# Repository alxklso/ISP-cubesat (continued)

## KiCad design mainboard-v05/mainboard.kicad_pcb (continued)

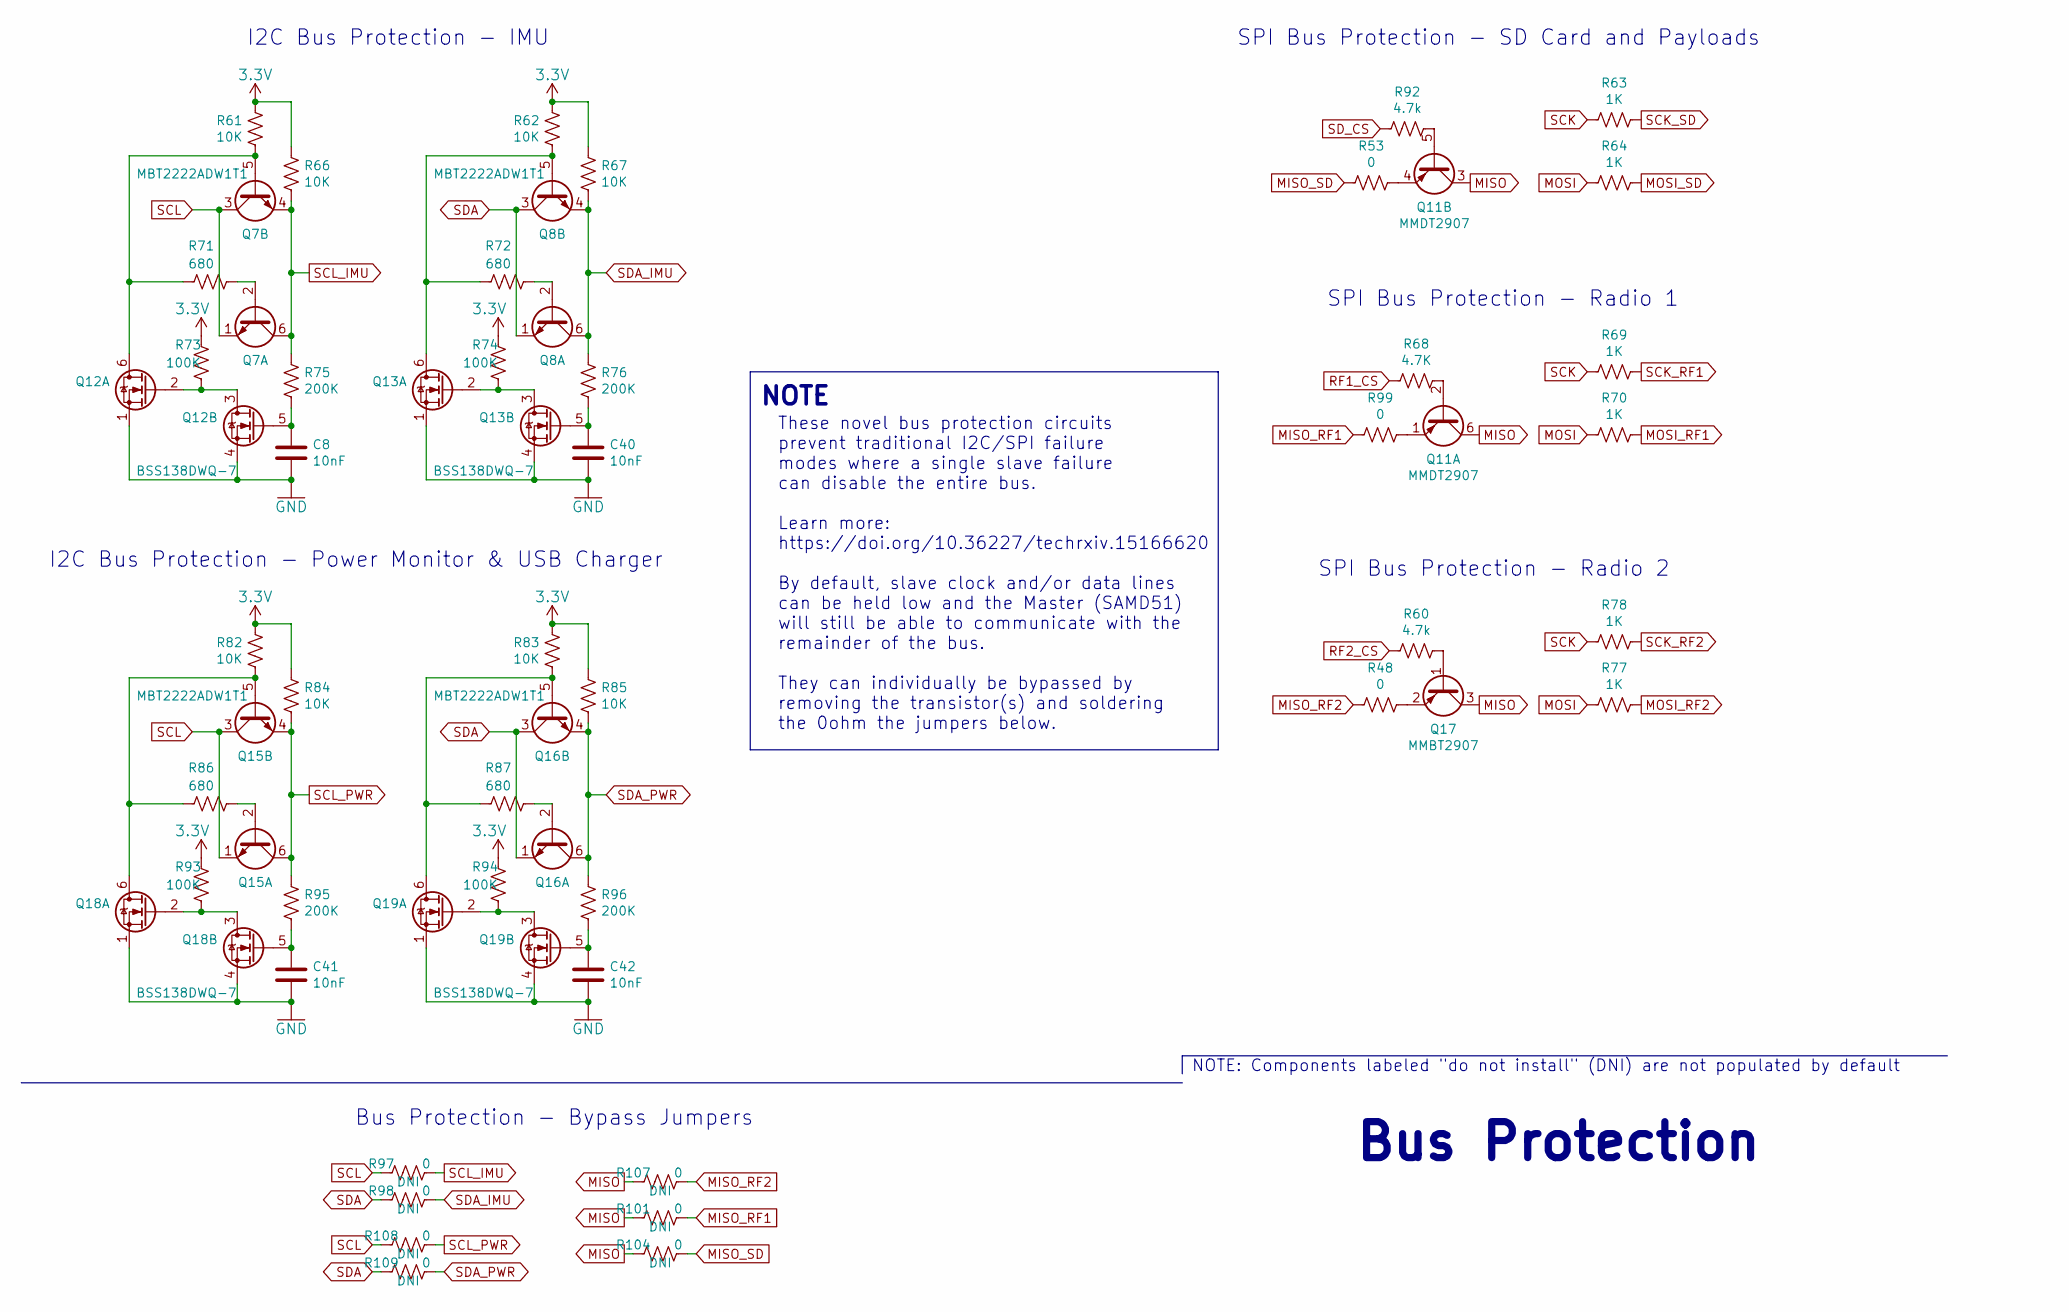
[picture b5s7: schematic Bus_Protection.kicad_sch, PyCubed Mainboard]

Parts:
C8, C40, C41, C42: 10nF; C_0603_1608Metric
Q7, Q8, Q15, Q16: MBT2222ADW1T1; SOT-363_SC-70-6; Manufacturer_Part_Number MBT2222ADW1T1G
Q11: MMDT2907; SOT-363_SC-70-6; Manufacturer_Part_Number MMDT2907AQ-7-F
Q12, Q13, Q18, Q19: BSS138DWQ-7; Manufacturer_Part_Number BSS138DWQ-7
Q17: MMBT2907; SOT-23; Manufacturer_Part_Number MMBT2907ALT1G
R48, R53, R97, R98, R99, R101, R104, R107, R108, R109: 0; R_0603_1608Metric
R60, R92: 4.7k; R_0603_1608Metric
R61, R62, R66, R67, R82, R83, R84, R85: 10K; R_0603_1608Metric
R63, R64, R69, R70, R77, R78: 1K; R_0603_1608Metric
R68: 4.7K; R_0603_1608Metric
R71, R72, R86, R87: 680; R_0603_1608Metric
R73, R74, R93, R94: 100K; R_0603_1608Metric
R75, R76, R95, R96: 200K; R_0603_1608Metric

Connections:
3.3V: R61.1, R62.1, R66.1, R67.1, R73.1, R74.1, R82.1, R83.1, R84.1, R85.1, R93.1, R94.1; also elsewhere on the board
GND: C8.2, C40.2, C41.2, C42.2, Q12.1 (S2), Q12.4 (S1), Q13.1 (S2), Q13.4 (S1), Q18.1 (S2), Q18.4 (S1), Q19.1 (S2), Q19.4 (S1); also elsewhere on the board
MISO: Q11.3 (C2), Q11.6 (C1), Q17.3 (C), R101.2, R104.2, R107.2; also elsewhere on the board
MISO_RF1: R99.2, R101.1; also elsewhere on the board
MISO_RF2: R48.2, R107.1; also elsewhere on the board
MISO_SD: R53.2, R104.1; also elsewhere on the board
MOSI: R64.2, R70.1, R77.2; also elsewhere on the board
MOSI_RF1: R70.2; also elsewhere on the board
MOSI_RF2: R77.1; also elsewhere on the board
MOSI_SD: R64.1; also elsewhere on the board
unnamed: C8.1, Q12.5 (G1), R75.2
unnamed: C40.1, Q13.5 (G1), R76.2
unnamed: C41.1, Q18.5 (G1), R95.2
unnamed: C42.1, Q19.5 (G1), R96.2
unnamed: Q7.2 (B1), R71.1
unnamed: Q8.2 (B1), R72.1
unnamed: Q11.1 (E1), R99.1
unnamed: Q11.2 (B1), R68.1
unnamed: Q11.4 (E2), R53.1
unnamed: Q11.5 (B2), R92.1
unnamed: Q12.2 (G2), Q12.3 (D2), R73.2
unnamed: Q7.5 (B2), Q12.6 (D1), R61.2, R71.2
unnamed: Q13.2 (G2), Q13.3 (D2), R74.2
unnamed: Q8.5 (B2), Q13.6 (D1), R62.2, R72.2
unnamed: Q15.2 (B1), R86.1
unnamed: Q15.5 (B2), Q18.6 (D1), R82.2, R86.2
unnamed: Q16.2 (B1), R87.1
unnamed: Q16.5 (B2), Q19.6 (D1), R83.2, R87.2
unnamed: Q17.1 (B), R60.1
unnamed: Q17.2 (E), R48.1
unnamed: Q18.2 (G2), Q18.3 (D2), R93.2
unnamed: Q19.2 (G2), Q19.3 (D2), R94.2
RF1_CS: R68.2; also elsewhere on the board
RF2_CS: R60.2; also elsewhere on the board
SCK: R63.2, R69.2, R78.2; also elsewhere on the board
SCK_RF1: R69.1; also elsewhere on the board
SCK_RF2: R78.1; also elsewhere on the board
SCK_SD: R63.1; also elsewhere on the board
SCL: Q7.1 (E1), Q7.3 (C2), Q15.1 (E1), Q15.3 (C2), R97.2, R108.2; also elsewhere on the board
SCL_IMU: Q7.4 (E2), Q7.6 (C1), R66.2, R75.1, R97.1; also elsewhere on the board
SCL_PWR: Q15.4 (E2), Q15.6 (C1), R84.2, R95.1, R108.1; also elsewhere on the board
SDA: Q8.1 (E1), Q8.3 (C2), Q16.1 (E1), Q16.3 (C2), R98.2, R109.2; also elsewhere on the board
SDA_IMU: Q8.4 (E2), Q8.6 (C1), R67.2, R76.1, R98.1; also elsewhere on the board
SDA_PWR: Q16.4 (E2), Q16.6 (C1), R85.2, R96.1, R109.1; also elsewhere on the board
SD_CS: R92.2; also elsewhere on the board

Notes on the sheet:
NOTE
Bus Protection - Bypass Jumpers
I2C Bus Protection - Power Monitor & USB Charger
SPI Bus Protection - Radio 1
These novel bus protection circuits prevent traditional I2C/SPI failure modes where a single slave failure can disable the entire bus. Learn more: https://doi.org/10.36227/techrxiv.15166620 By default, slave clock and/or data lines can be held low and the Master (SAMD51) will still be able to commu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
NOTE: Components labeled "do not install" (DNI) are not populated by default
I2C Bus Protection - IMU
SPI Bus Protection - Radio 2
SPI Bus Protection - SD Card and Payloads
Bus Protection

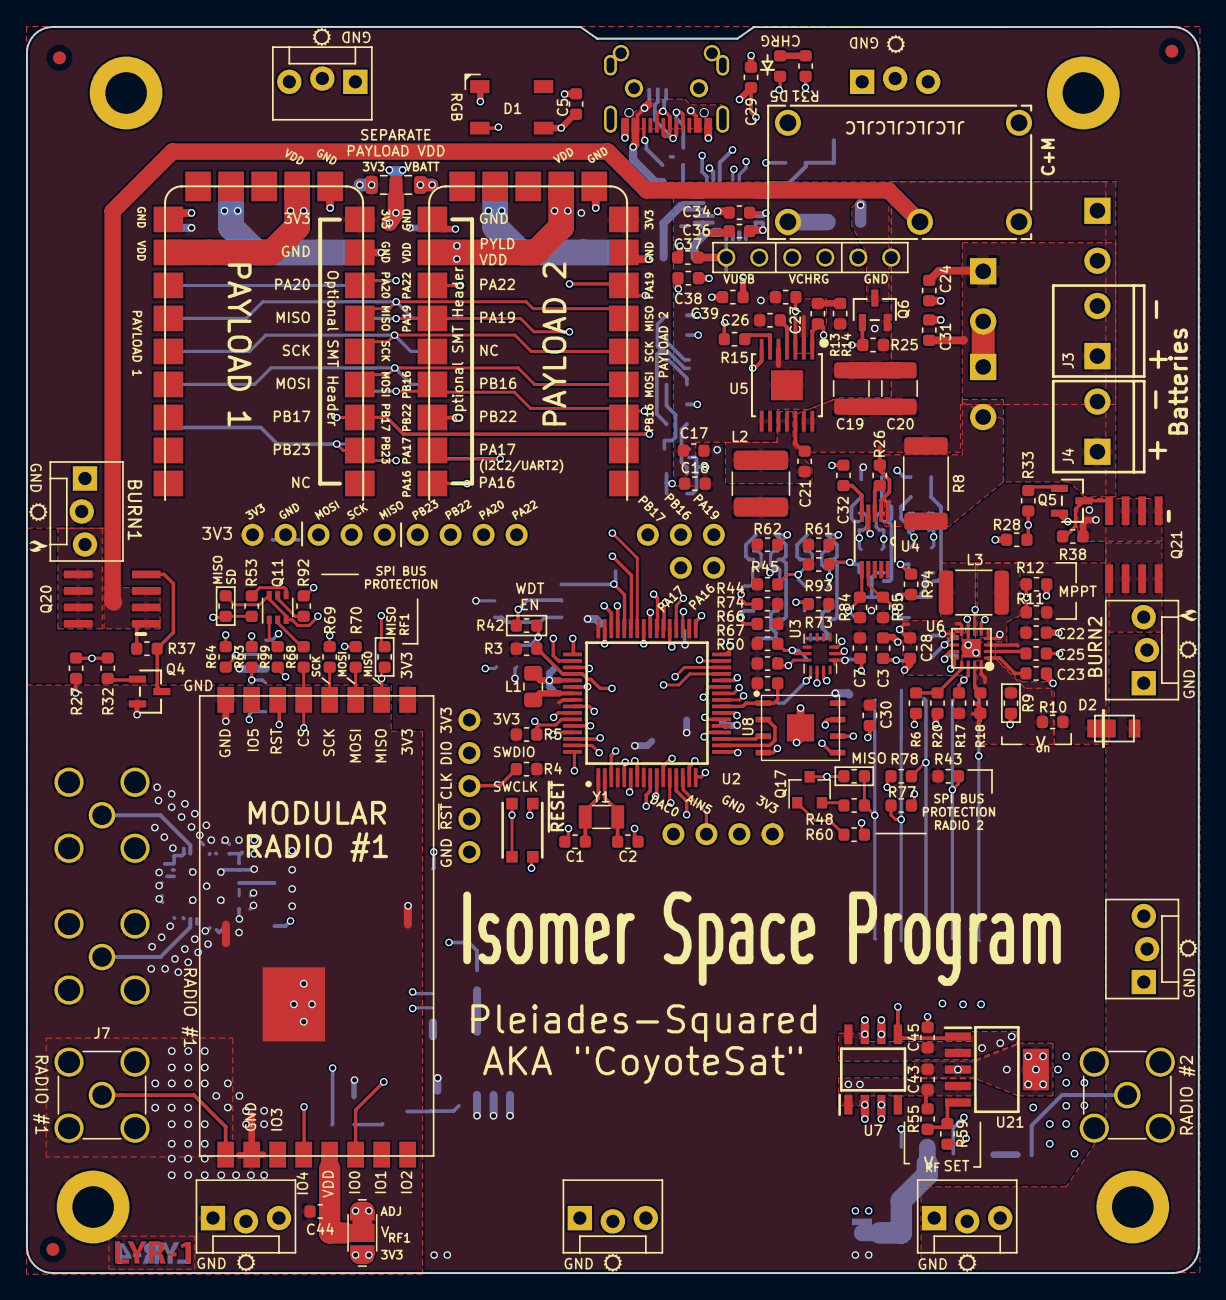
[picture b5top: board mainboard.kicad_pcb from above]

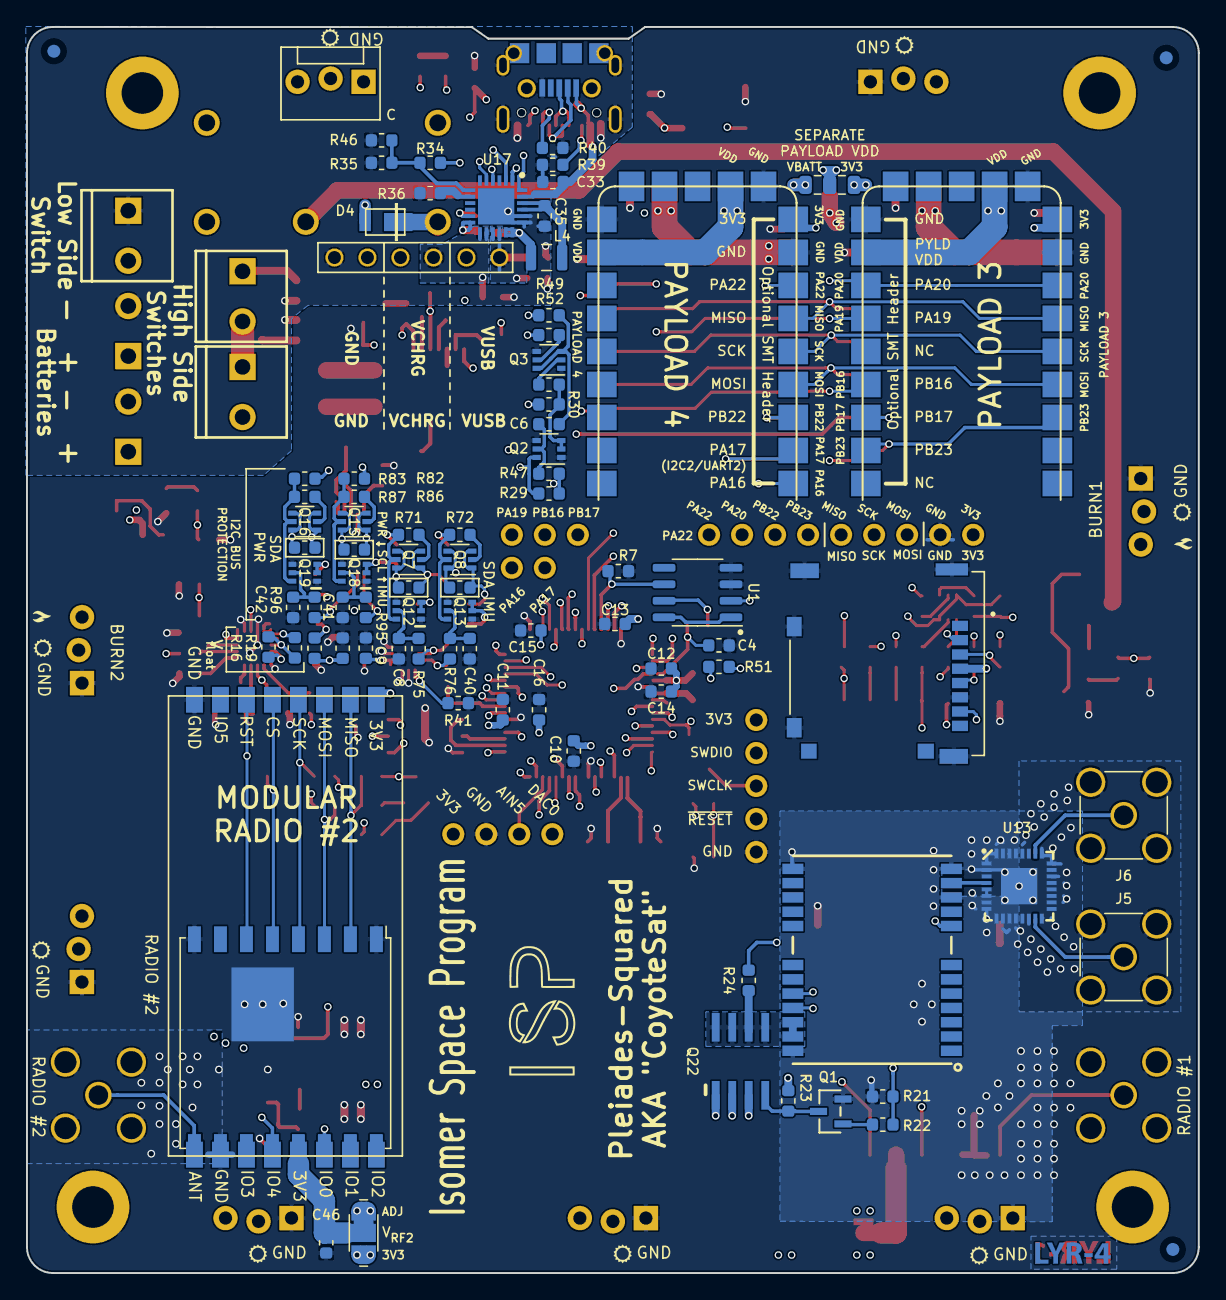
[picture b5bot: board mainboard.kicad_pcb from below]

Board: 4 copper layers, 90.2 x 95.9 mm, 230 parts (91 on the bottom side), 160 nets.

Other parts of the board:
REF1B, REF1T, REF2B, REF2T, REF3B, REF3T: Fiducial_1mm_Mask2mm

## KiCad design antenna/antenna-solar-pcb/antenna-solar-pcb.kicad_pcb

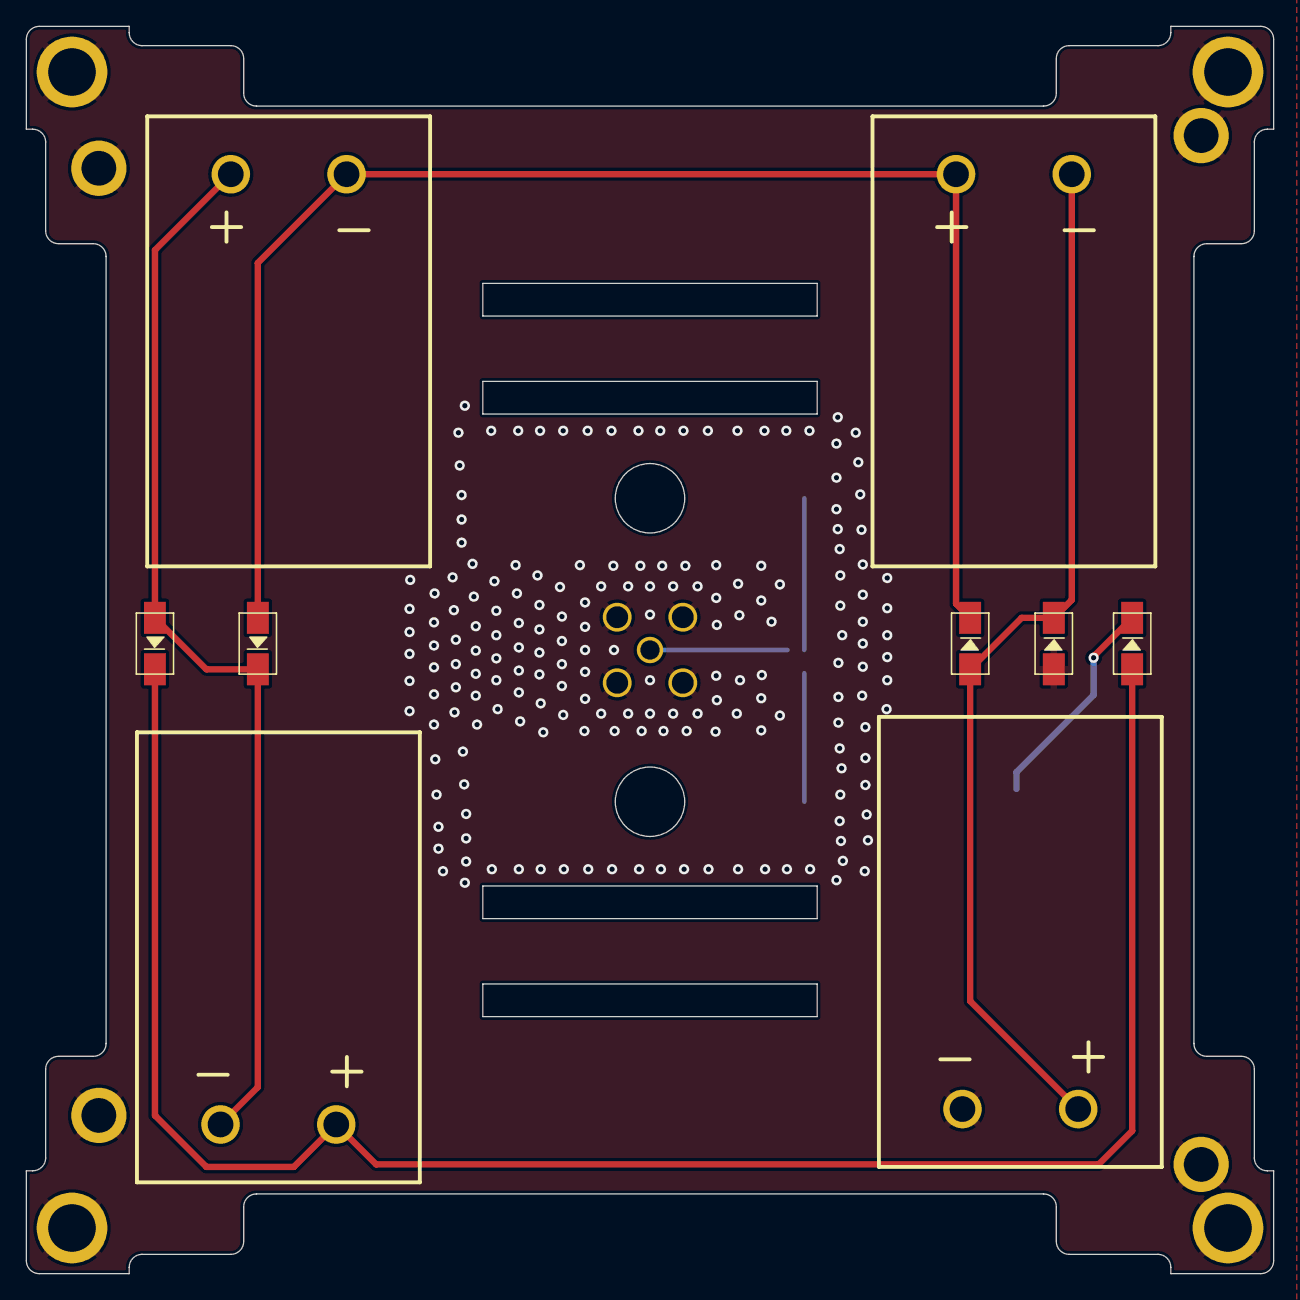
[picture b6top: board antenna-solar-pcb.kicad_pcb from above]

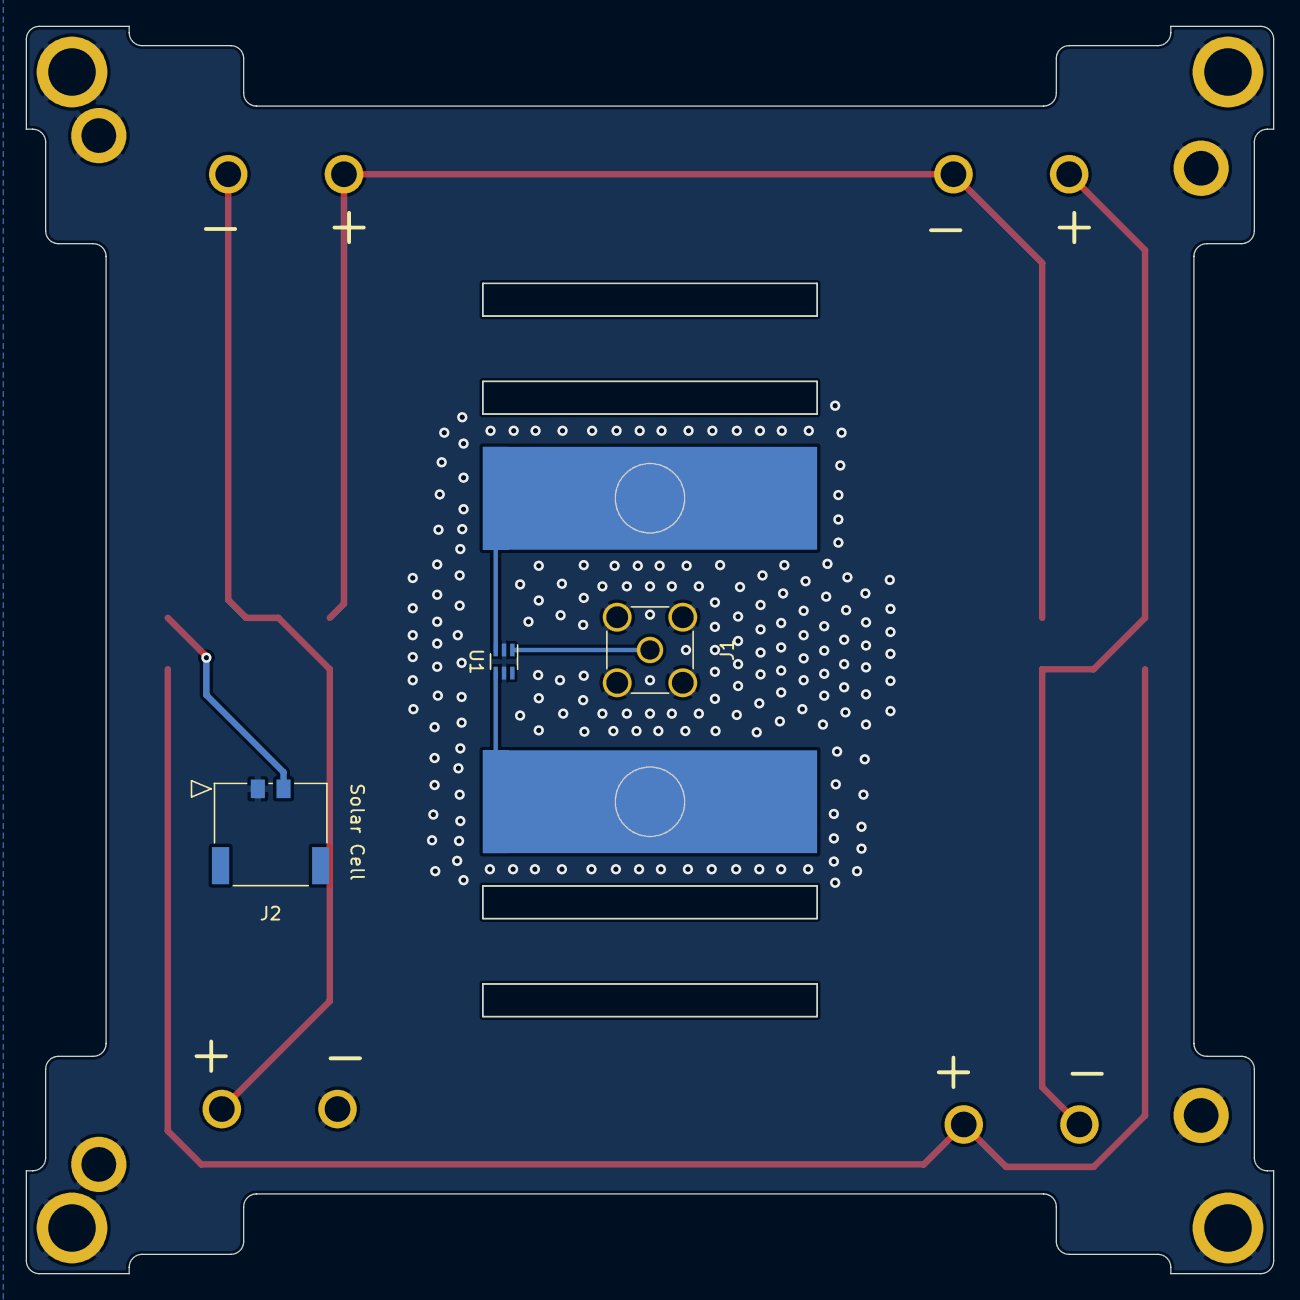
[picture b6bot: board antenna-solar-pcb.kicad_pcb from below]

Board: 2 copper layers, 97.0 x 97.0 mm, 21 parts (4 on the bottom side), 9 nets.

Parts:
AE1: Dipole_Antenna; Antenna_Pads
D1, D2, D3, D4, D5: CDBA240LL-HF; DO-214AC
H1, H2, H3, H4: MountingHole_Pad; MountingHole_3.7mm_Pad_Modified
H5, H6, H7, H8: MountingHole_Pad; MountingHole_2.7mm_M2.5_DIN965_Pad
J1: SMA Connector Male; SMA_Connector
J2: Solar Cell; pico_lock_2mm_2circuit
SC1, SC2, SC3, SC4: SM101K07TF
U1: HHM1589D1; Balun_Johanson_5400BL15B050E

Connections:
GND: D4.2 (A), H1.1, H2.1, H3.1, H4.1, H5.1, H6.1, H7.1, H8.1, J1.2 (Ext), J2.1, SC4.2 (-), U1.2 (GND), U1.5 (GND)
unnamed: AE1.1, U1.3 (Balanced_Port)
unnamed: AE1.2, U1.4 (Balanced_Port)
unnamed: D1.1 (K), D5.2 (A), SC1.1 (+)
unnamed: D1.2 (A), D2.1 (K), SC1.2 (-), SC2.1 (+)
unnamed: D2.2 (A), D3.1 (K), SC2.2 (-), SC3.1 (+)
unnamed: D3.2 (A), D4.1 (K), SC3.2 (-), SC4.1 (+)
unnamed: J1.1 (In), U1.1 (Balanced_Port)
VSOLAR: D5.1 (K), J2.2

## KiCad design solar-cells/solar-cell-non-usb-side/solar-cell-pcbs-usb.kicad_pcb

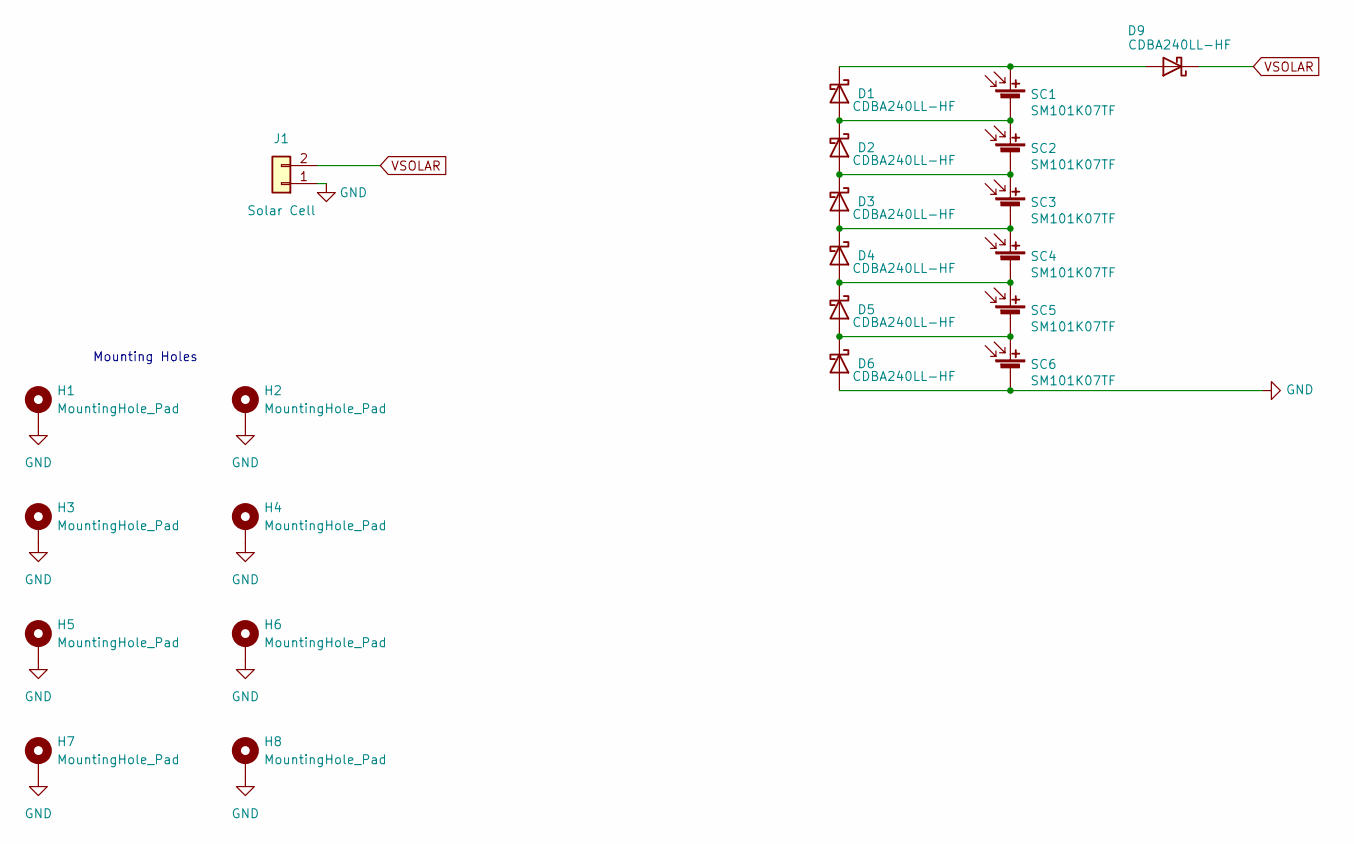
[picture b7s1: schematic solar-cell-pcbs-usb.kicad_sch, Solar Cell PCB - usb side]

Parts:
D1, D2, D3, D4, D5, D6, D9: CDBA240LL-HF; DO-214AC
H1, H2, H3, H4, H5, H6, H7, H8: MountingHole_Pad; MountingHole_3.2mm_M3_DIN965_Pad
J1: Solar Cell; 2053380002
SC1, SC2, SC3, SC4, SC5, SC6: SM101K07TF

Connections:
GND: D6.2 (A), H1.1, H2.1, H3.1, H4.1, H5.1, H6.1, H7.1, H8.1, J1.1, SC6.2 (-)
unnamed: D1.1 (K), D9.2 (A), SC1.1 (+)
unnamed: D1.2 (A), D2.1 (K), SC1.2 (-), SC2.1 (+)
unnamed: D2.2 (A), D3.1 (K), SC2.2 (-), SC3.1 (+)
unnamed: D3.2 (A), D4.1 (K), SC3.2 (-), SC4.1 (+)
unnamed: D4.2 (A), D5.1 (K), SC4.2 (-), SC5.1 (+)
unnamed: D5.2 (A), D6.1 (K), SC5.2 (-), SC6.1 (+)
VSOLAR: D9.1 (K), J1.2

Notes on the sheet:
Mounting Holes

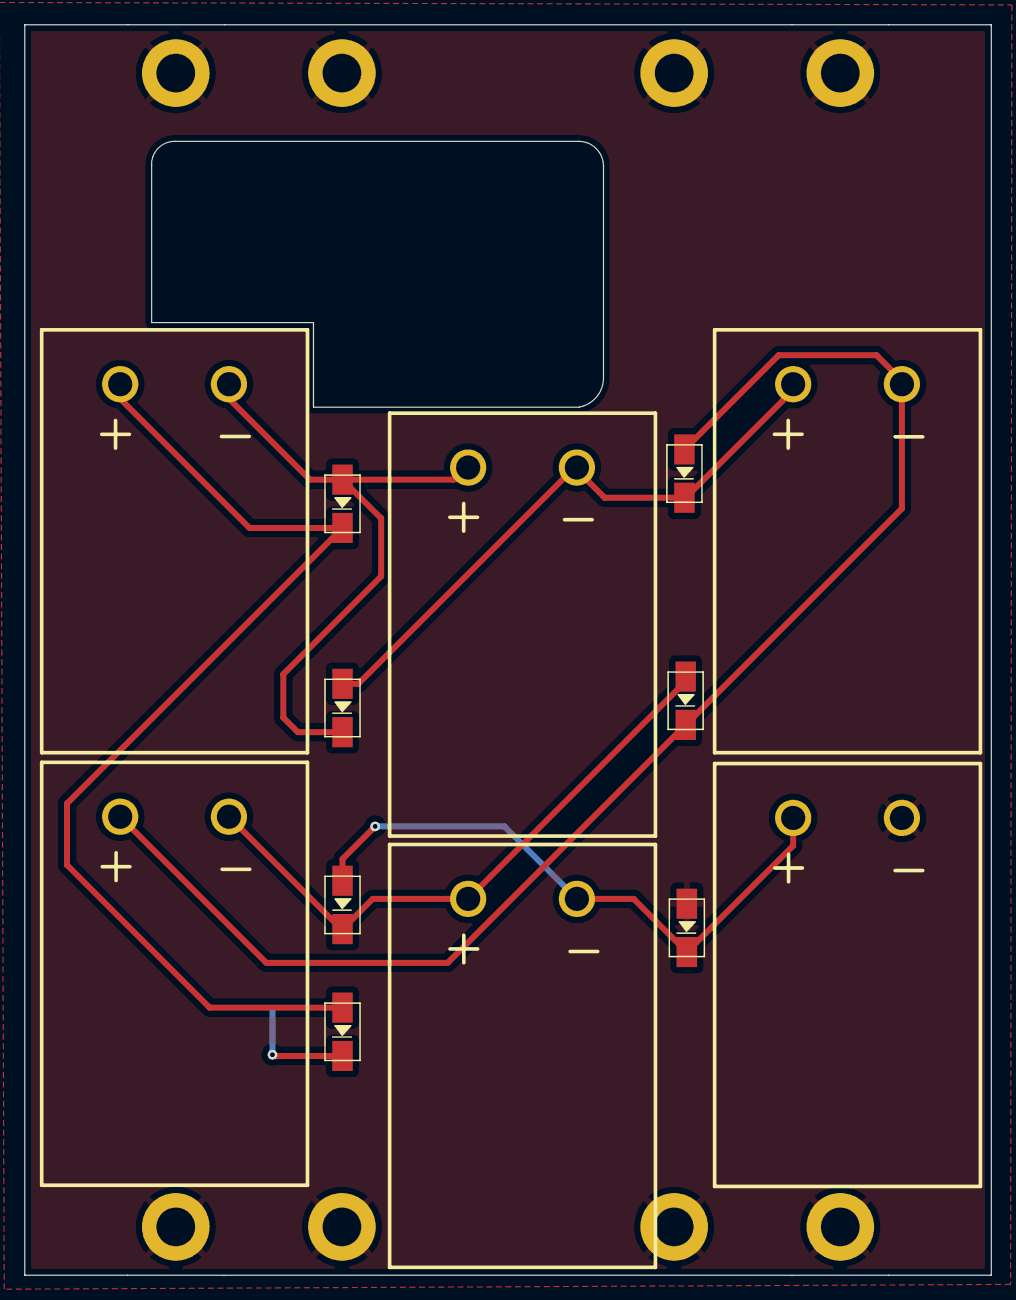
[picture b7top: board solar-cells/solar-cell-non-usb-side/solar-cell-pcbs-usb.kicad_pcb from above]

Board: 2 copper layers, 80.0 x 103.5 mm, 22 parts (1 on the bottom side), 8 nets.

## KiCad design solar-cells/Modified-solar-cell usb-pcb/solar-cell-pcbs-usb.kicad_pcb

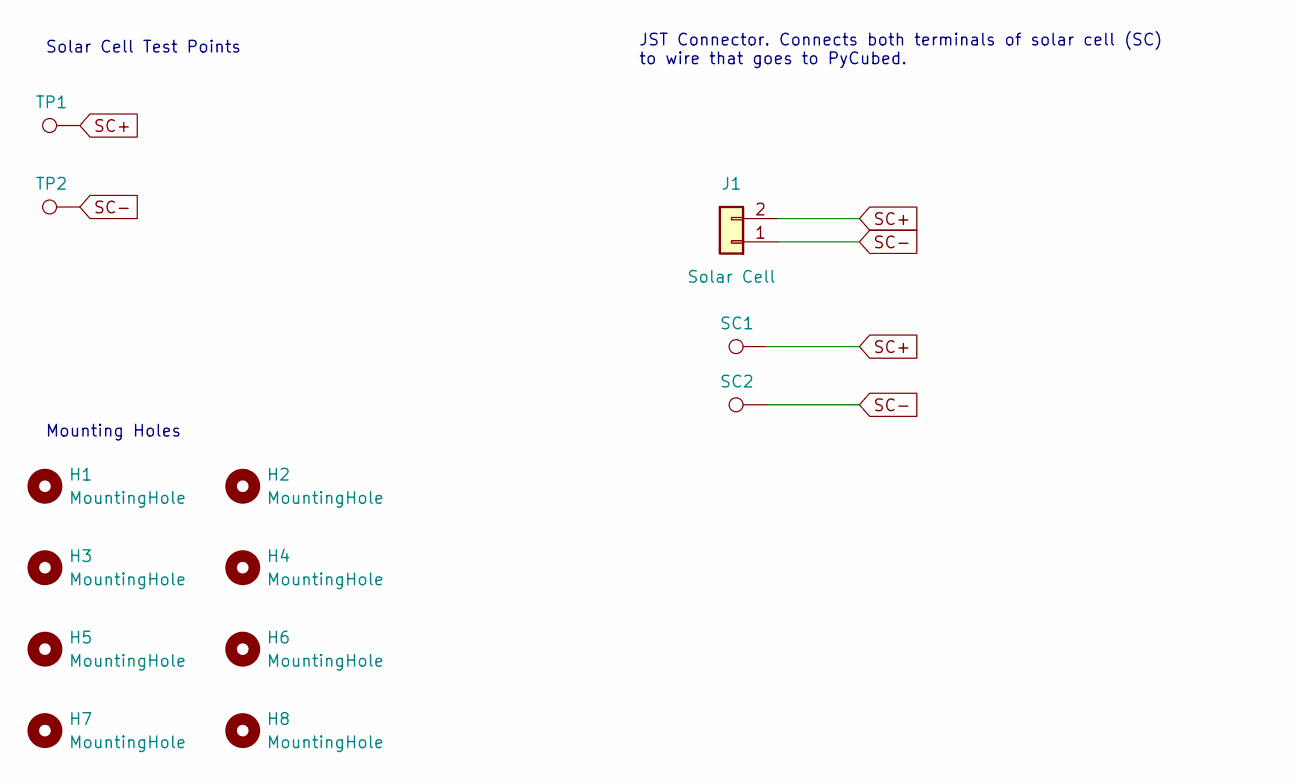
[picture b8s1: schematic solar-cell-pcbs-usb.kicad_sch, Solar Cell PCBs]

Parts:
H1, H2, H3, H4, H5, H6, H7, H8: MountingHole; MountingHole_3.2mm_M3_DIN965_Pad
J1: Solar Cell; 2053380002
SC1: SC+; TestPoint_THTPad_D3.0mm_Drill1.5mm
SC2: SC-; TestPoint_THTPad_D3.0mm_Drill1.5mm
TP1: SC+; TestPoint_Loop_D1.80mm_Drill1.0mm_Beaded
TP2: SC-; TestPoint_Loop_D1.80mm_Drill1.0mm_Beaded

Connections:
SC+: J1.2, SC1.1, TP1.1
SC-: J1.1, SC2.1, TP2.1

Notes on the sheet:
Solar Cell Test Points
Mounting Holes
JST Connector. Connects both terminals of solar cell (SC) to wire that goes to PyCubed.

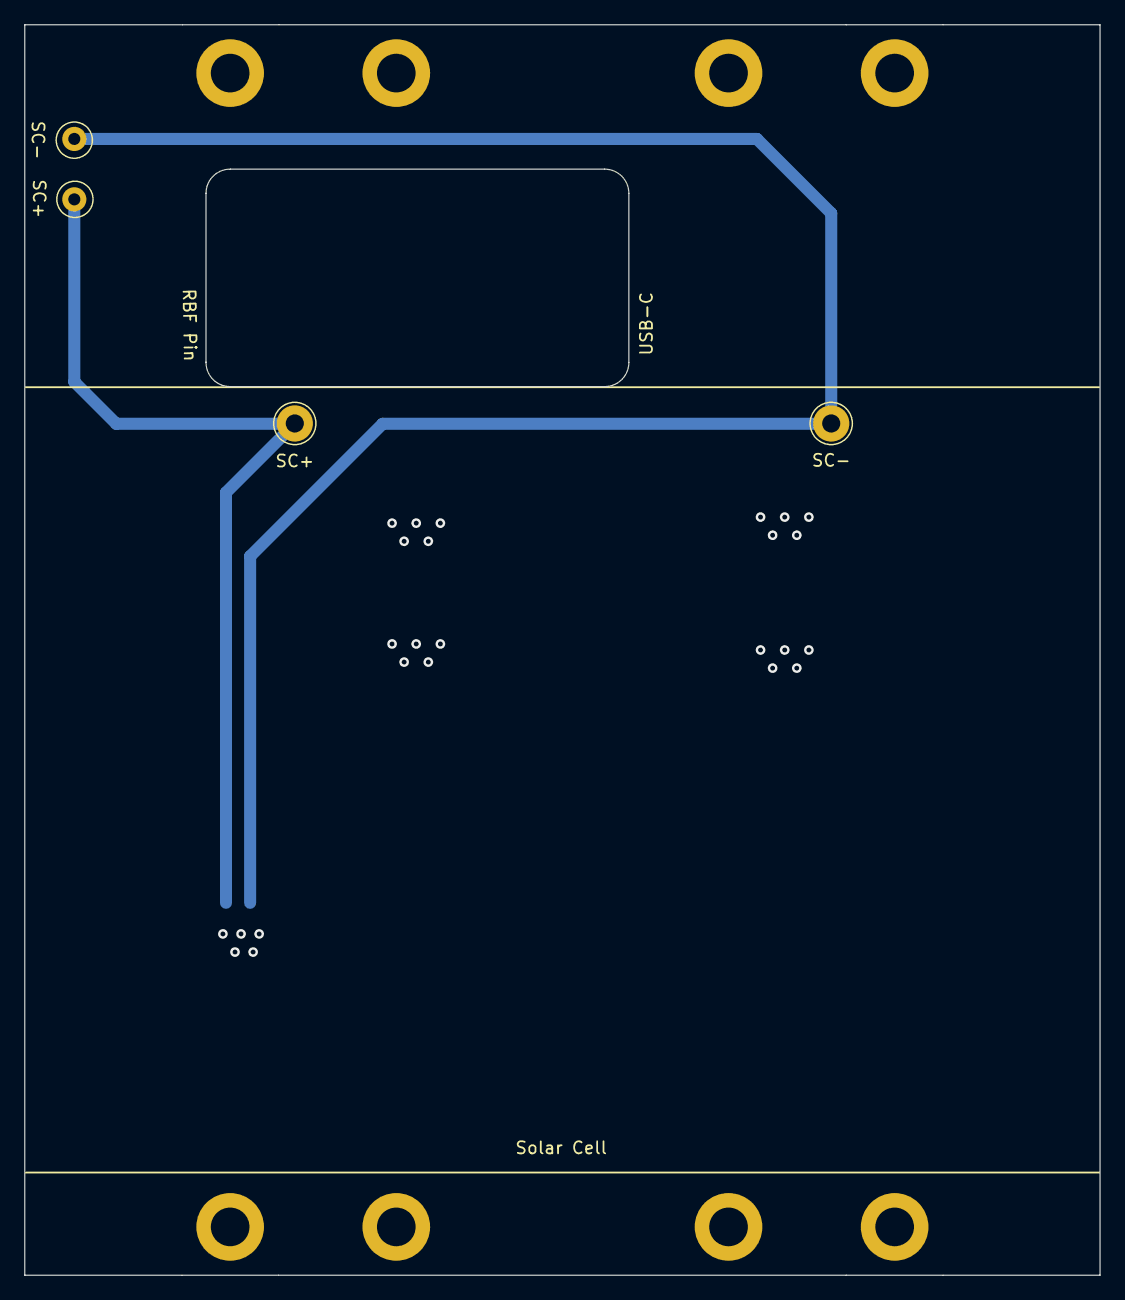
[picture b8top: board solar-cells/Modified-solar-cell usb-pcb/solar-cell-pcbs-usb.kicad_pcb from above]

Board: 2 copper layers, 89.0 x 103.5 mm, 13 parts (1 on the bottom side), 2 nets.

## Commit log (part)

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2022-07-16 Add files via upload
    gerber files for modified battery board
2022-07-21 Create blink.py
    Added prototyping and thing plus board folders, as well as blink test python file
2022-07-21 Add files via upload
    added light sensor test python file
2022-07-21 Create blink.py
    added new prototyping file and blink test python file
2022-07-21 Add files via upload
    added blink and light_sensor test python files for use with Thing Plus board (prototyping)
2022-08-15 Update light_sensor.py
    added more comments
2022-08-15 Add files via upload
    This is a file that does a simple channel scan for the TCA9548A multiplexer using a SAMD51 Thing Plus
2022-08-15 Rename light_sensor.py to ambient_light_sensor.py
    renamed
2022-08-15 Add files via upload
    Program for single VEML7700 lux sensor added
2022-08-19 Add files via upload
    Added file-writing functionality for sensor data
2022-08-19 Update four_lux_sensors.py
    fixed file format
2022-08-30 reorganized prototype folder
2022-08-30 added basic beepsat
2022-08-30 added mainboard files
2022-08-30 Update README.md
    Added annotations in README
2022-08-30 Update README.md
    Edited README
2022-09-07 added more prototyping folders
2022-09-07 fix again
2022-09-07 fixed file structure
2022-09-07 added more notes to README
2022-09-07 more notes to README
2022-09-24 added radio test software
2022-10-08 deleted IMU code
2022-10-12 added power consumption test py script
2022-10-15 added asyncioTest file
2022-10-15 lil fixes to asyncioTest
2022-10-18 adjusted code for Python 3.x syntax
2022-10-19 code changes to CW py script
2022-10-29 added test code for SD
2022-11-06 removed options 2,3, and moved up option 4 for script menu
2022-11-07 refactoring + deleting help info printing
2022-11-07 created datasheets folder and added solar cells data sheet
2022-11-12 re-uploaded beepsat-basic
2022-11-12 fixed formatting + module import error in main
2022-11-12 removed IMU code since no IMU is installed
2022-11-12 Added cosmic watch task file, and further formatting/annotating
2022-11-12 annotating main
2022-11-12 added gitignore
2022-11-12 Create LICENSE.md
    Added MIT License
2022-11-14 changed file layout
2022-11-16 added py script for logging CW data in terminal via USB
2022-11-16 added file-writing to CW datalogging script
2022-11-21 made separate folder for all CW stuff
2022-11-23 Updated CW script w file-writing and sample data file
2022-11-23 updated comments to serial port script
2022-11-23 moved comments to inside main
2022-12-09 added most recent sdWrite py script
2022-12-09 removed sdWrite file from beepsat-basic FSW, use the one in prototyping-CW until finalized
2022-12-09 updated CW script w/ comments and refactoring
2022-12-09 fix attempt
2022-12-10 Removed unnecessary sections of OLED arduino code
2022-12-12 made separate file for Arduino code to be used in space
2022-12-12 fixed CW task
2022-12-12 CW task now records data for 1 minute interval, still need to escape task tho
2022-12-12 modified main to be more helpful during debugging
2022-12-13 added radio test script and modified sdWrite to proto-pycubed folder
2022-12-13 Delete software/proto-CW/.idea directory
    deleted idea files
2022-12-18 Modified Arduino code to only record sipm voltage, also renamed OLED --> space
2022-12-18 Reorganized Arduino folder and updated README
2022-12-18 removed GPS and radio2 code
2022-12-19 new folder and kicad project for solar cell pcbs
2022-12-20 modified batt board to have wiring cutouts
2022-12-20 modifications to solar cell pcb
2022-12-21 modifications to solar cell pcbs with burn wires and usb cut out
2022-12-21 centering
2022-12-21 modifications to solar cell folder
2022-12-23 Create HI
2022-12-24 added cutouts and moved SMA connection point on mainboard
2022-12-25 fixed SMA connector issue and board cutouts
2022-12-25 sanity check commit
2022-12-25 added non-usb solar cell pcb side
2022-12-25 more annotations and connected test points
2022-12-25 removed thermal vias and fixed silkscreen
2022-12-25 change burn wire solar cell pcb to vertical
2022-12-25 removed OG usb solar cell pcb folder, not needed anymore
2022-12-25 modify non usb pcb
2022-12-25 name changes
2022-12-26 added more annotations
2022-12-26 update gitignore
2022-12-26 changes to non usb side
2022-12-26 changes to routes in burn wire pcb
2022-12-26 fixed mismatched traces
2022-12-26 measurement checking for non-usb and vertical burn pcbs
2022-12-26 remove silkscreen on footprint
2022-12-26 gerbers for non-usb and vertical burn created
2022-12-30 added beepsat advanced code
2022-12-30 deleted gps, radio2, and imu code
2022-12-30 fixed and formatted main
2022-12-30 added task for Cosmic Watch
2022-12-30 reformatting
2022-12-30 more formatting
2022-12-31 added antenna pcb folder
2022-12-31 create antenna pcb kicad prohect
2022-12-31 modified antenna pcb
2022-12-31 add antenna pcb with two slits on each side
2022-12-31 modify antenna pcbs and drc checked
2022-12-31 removed md file
2022-12-31 annotations
2022-12-31 fix dimensions
2022-12-31 add dimensions
2022-12-31 change sma connector hole size
2022-12-31 add kicad lib
2023-01-01 updated schematic for new solar cells
2023-01-01 hole positioning
2023-01-01 solar cell pcb laid out
2023-01-01 added usbc hole
2023-01-01 no edgecuts errors
2023-01-01 traces added
2023-01-01 new solar cell for burn wire side
2023-01-01 added silkscreens
2023-01-01 fixed mounting holes
2023-01-01 hole fixing
2023-01-01 hole removal
2023-01-01 directory reorg
2023-01-01 add new new solar cell pcb for burn wire side
2023-01-01 removed extra measurements from new new
2023-01-01 fixing up usb side
2023-01-01 check for new new
2023-01-01 created bottom adapter plate w/ solar cells
2023-01-01 bottom adapter plate sanity commit
2023-01-01 placed components, added traces to antenna-solar
2023-01-01 added screw holes for antennas in antenna-solar
2023-01-02 adjusted for limit switches allowance
2023-01-02 moved GND hole to not interfere w/ chassis beam
2023-01-02 aligned burn wire holes
2023-01-02 added test software file for before + after vibration testing
2023-01-02 added pycubed.py and libraries to test software
2023-01-03 fixed annotations
2023-01-03 fixed disconnected track
2023-01-03 changed burn wire to 3s2p config
2023-01-03 fixed tracks to reduce EMI
2023-01-03 fixed bottom adapter to be 3s2p
2023-01-03 fixed tracks, added vias
2023-01-03 fixed routing, added vias
2023-01-03 final commit for bottom adapter w/ solar
2023-01-05 Moved item into loop
2023-01-06 rotated JST, fixed batt holder holes
2023-01-06 fixed something weird
2023-01-06 Revert "Moved item into loop"
    This reverts commit 62312068ed386dce9a1a4cf67fe31766c9685957.
2023-01-06 Revert "Added initial i2c code"
    This reverts commit f7e053b2185c1d86999f7e089d7532763f734a9c.
2023-01-06 added ISP graphic to mainboard
2023-01-06 Added file chunking
2023-01-06 Added message packing
2023-01-19 added startup routine to main
2023-01-25 updated datasheets
2023-02-06 updated antenna pcb
2023-02-06 added new solar panels w removed burn wires
2023-02-06 removed solar panels from bottom adapter and moved burn connector
2023-02-06 few touches and measurements to working solar panel usb side
2023-02-08 added updated bottom adapter w/ silkscreen
2023-02-09 fixed zoning and burn pads
2023-02-09 fixed balun placement and wiring
2023-02-13 sanity push
2023-02-13 new batt board and bottom adapter w/ fixed silkscreen
2023-02-19 deleted fasw basic
2023-02-19 added full radio test script for pycubed
2023-02-19 added arduino code for tx and rx -- need to download local copy of libraries
2023-02-19 fixed formatting issue
2023-02-19 added radio 2 define and init code to pycubed.py
2023-02-19 added irvin's system health check software
2023-02-22 added plus and minus labels for solar panel terminals
2023-02-22 added ground holes
2023-02-22 added measurements to antenna pcb
2023-02-22 updated archived
2023-02-27 add assembly and test notes
2023-02-27 add firmware folder
2023-03-02 added opposite-usb side
2023-03-05 update hardware tracker
2023-03-17 Updated bottom plate kicad file to kicad 7
2023-03-17 Added text for special thanks to
2023-03-17 Aligned special thanks to text
2023-03-17 Fixed alignment for special thanks to
2023-03-17 Added quotes
2023-03-18 Fixed quote spacing kicad
2023-03-18 Removed quotes title
2023-03-18 Fixed name
2023-03-18 New gerbers
2023-03-18 Updated gerbers for bottom adapter
2023-03-18 Added feather radio code
2023-03-19 Fixed bottom adapter
2023-03-31 local
2023-04-14 Fix stupid windows bug with filenames
2023-04-14 Fix windows bug pt 2
2023-04-14 Updated main.py with burn bits
2023-04-14 Swapped i2c
2023-04-16 more fixes in pycubed and main
2023-04-16 fuck
2023-04-16 Added sleep for waiting for burn wire
2023-04-16 Added normal power mode to startup
2023-04-16 Added low batt flag
2023-04-16 Fixed import for alarm
2023-04-16 sanity commit
2023-04-18 Added base library to i2c prototype
2023-04-18 Added adafruit specific library to i2c prototype
2023-04-19 added most recent ground station code
2023-04-19 comments and defined COYOTESAT params
2023-04-19 Set send data to false
2023-04-19 Moved prototyping i2c into task backbone
2023-04-19 Fixed i2c
2023-04-19 Enable CW task
2023-04-19 Added adafruit lib to fm src
2023-04-19 Upped cw task back to 60s
2023-04-19 Added flags for testing
2023-04-19 Added configuration into main.py
2023-04-19 Added burn flag
2023-04-19 Removed degenerate comment
2023-04-19 Added sleeping for benchtop testing
2023-04-19 Disable sleep when benchtop testing
2023-04-19 Added launch instructions
2023-04-19 Update sleep alarm for benchtop testing
2023-04-19 Moved launch instructions
2023-04-19 Remove blink task
2023-04-20 Fixed indent
2023-04-20 tidying up
2023-04-20 more tidying up
2023-04-20 refactored hard reset in main
2023-04-20 adding f-strings and more tidying
2023-04-21 added datasheets
2023-04-21 added txt file of donors
2023-04-22 Cleaned up radio definitions
2023-04-22 Fixed radiopacket array size
2023-04-23 Fixed radio frequency for feather board
2023-04-23 Cleaned up names by adding those from google sheets too + removed duplicates
2023-04-23 Revert "Cleaned up names by adding those from google sheets too + removed duplicates"
    This reverts commit 8182504ca77e6a650fa18d44893b3bab4b341e1a.
2023-04-24 Swap lowbat to end
2023-04-24 Moved lowbatt again
2023-04-24 add startup radio beacon
2023-04-24 added identifiers at beginning and end of radio messages, need to fix ID beacon at beginning
2023-04-24 refactoring, commenting
2023-04-24 TODO for new ADC lib on CW
2023-04-24 Fixed antenna attached
2023-04-24 Cleaned up pycubed code
2023-04-26 Fixed typo
2023-04-26 Added new libs
2023-04-26 Added antenna attached check
2023-04-26 Added extra precautions for radio
2023-04-27 Ignore vscode
2023-04-27 Fixed git ignore
2023-04-27 Cleaned up codebase
2023-04-27 Fixed git again
2023-04-27 Added radio call sign to everything
2023-04-27 Fixed docs
2023-04-27 Added file deletion logic
2023-04-27 Fixed spreading factor
2023-04-27 Cleaned up start up alert
2023-04-28 Cleaned up cw
2023-04-28 Cleaned up beacon
2023-04-28 Cleaned up main
2023-04-28 Cleaned up pycubed
2023-04-28 Cleaned up cdh
2023-04-28 Fixed rfm lib
2023-04-28 Schedule later for daily reset
2023-04-28 Improved sleep for testing
2023-04-28 Added error catching + fixed params
2023-04-28 Cleared out faulty code for now
2023-04-28 Fixed priorities
2023-04-28 Updated bytes for cw
2023-04-28 Added benchtop testing for cw
2023-04-28 Added catching for sd card not existing
2023-04-28 Fixed beacon logging
2023-04-28 Fixed testing checks
2023-04-28 Set listening timeout for testing
2023-04-28 Fixed path
2023-04-28 Clean up path
2023-04-28 Handle sd card properly
2023-04-28 Fix directory checks
2023-04-28 Fix edge case where dir doesn't exist
2023-04-28 Switch to using debug
2023-04-28 Removed logging chunk
2023-04-28 Fixed logging
2023-04-28 Fixed max files
2023-04-28 Fixed frequencies
2023-04-28 Switched to storing only a single file
2023-04-28 Added try catches
2023-04-29 Cleaned up sending
2023-04-29 Add pycubed radio test
2023-05-23 added measurements to usb side solar panels
2023-05-23 added measurements for opposite usb
2023-05-23 updating comments
